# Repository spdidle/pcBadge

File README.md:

# Fallout PCB Badge!
haii this pcb badge is a stupidly simple camera so you can clip your friends and keep the memory forever :p

# Schematic

# PCB 1

# PCB 2

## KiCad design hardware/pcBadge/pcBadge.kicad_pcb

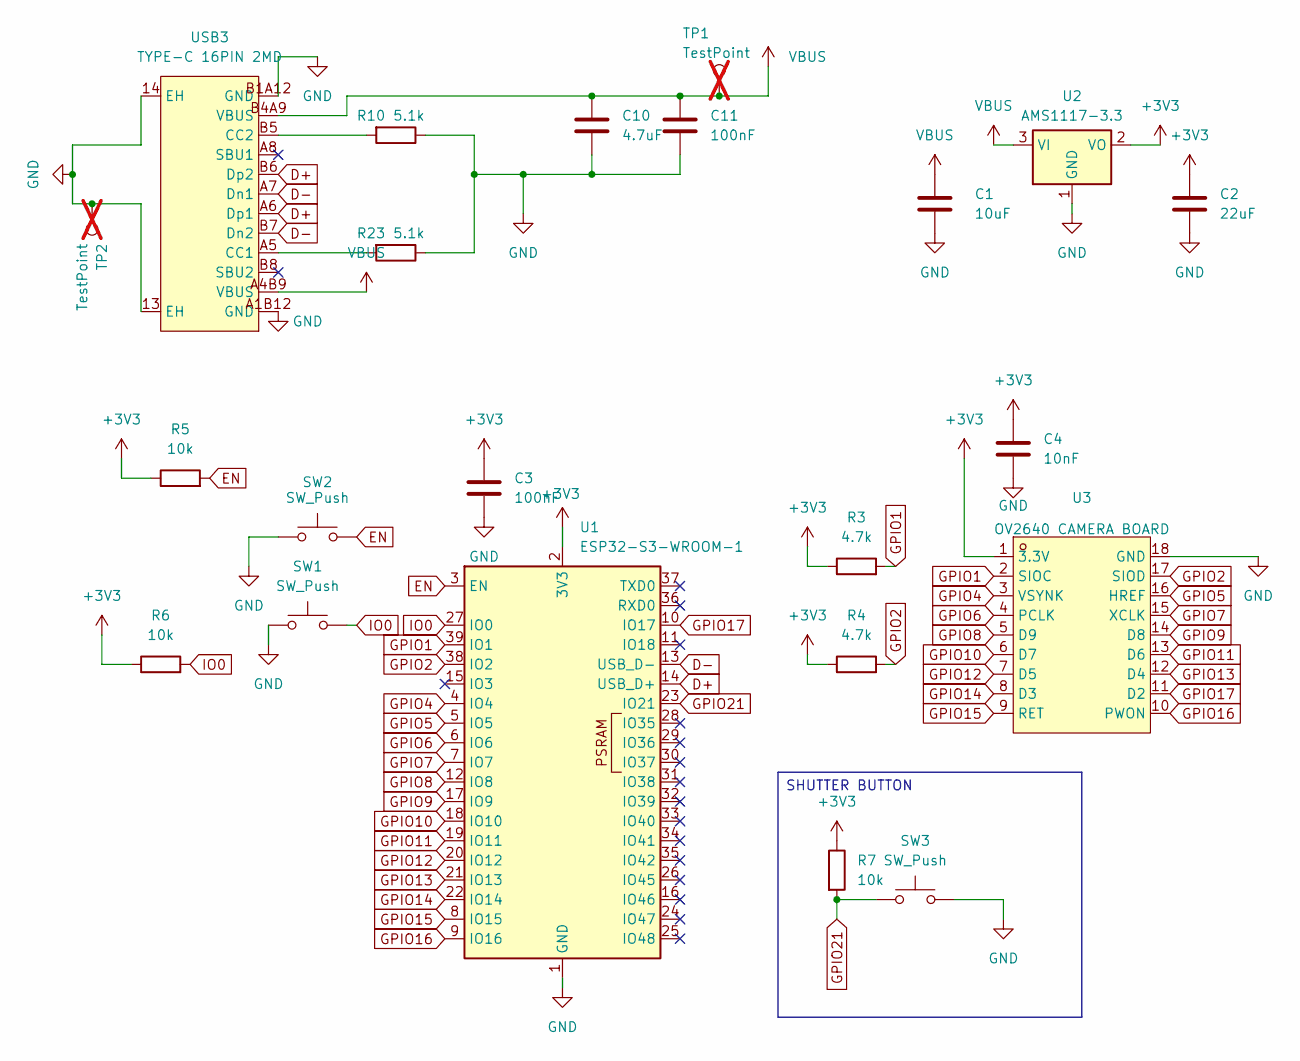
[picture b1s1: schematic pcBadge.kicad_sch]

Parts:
C1: 10uF; C_0805_2012Metric_Pad1.18x1.45mm_HandSolder
C2: 22uF; C_0805_2012Metric_Pad1.18x1.45mm_HandSolder
C3: 100nF; C_0805_2012Metric_Pad1.18x1.45mm_HandSolder
C4: 10nF; C_0805_2012Metric_Pad1.18x1.45mm_HandSolder
C10: 4.7uF; C_0805_2012Metric
C11: 100nF; C_0805_2012Metric
R3, R4: 4.7k; R_0805_2012Metric_Pad1.20x1.40mm_HandSolder
R5, R6, R7: 10k; R_0805_2012Metric_Pad1.20x1.40mm_HandSolder
R10, R23: 5.1k; R_0805_2012Metric
SW1, SW2: SW_Push; SW_Push_SPST_NO_Alps_SKRK
SW3: SW_Push; SW_PUSH-12mm
TP1, TP2: TestPoint; TestPoint_Pad_D1.0mm; not fitted
U1: ESP32-S3-WROOM-1
U2: AMS1117-3.3; SOT-223-3_TabPin2
U3: OV2640 CAMERA BOARD; SENSORM-TH_L35.7-W3.9-OV2640; MPN OV2640 Camera Board; LCSC Part C359962
USB3: TYPE-C 16PIN 2MD; USB-C-SMD_TYPE-C-16PIN-2MD-073; MPN TYPE-C 16PIN 2MD(073); LCSC Part C2765186

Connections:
+3V3: C2.1, C3.1, C4.1, R3.1, R4.1, R5.1, R6.1, R7.1, U1.2 (3V3), U2.2 (VO), U3.1 (3.3V)
D+: U1.14 (USB_D+), USB3.A6 (Dp1), USB3.B6 (Dp2)
D-: U1.13 (USB_D-), USB3.A7 (Dn1), USB3.B7 (Dn2)
EN: R5.2, SW2.2, U1.3 (EN)
GND: C1.2, C2.2, C3.2, C4.2, C10.1, C11.2, R10.1, R23.1, SW1.1, SW2.1, SW3.2, TP2.1 (1_1), U1.1 (GND), U1.40 (GND), U1.41 (GND), U2.1 (GND), U3.18 (GND), USB3.13 (EH), USB3.14 (EH), USB3.A1B12 (GND), USB3.B1A12 (GND)
GPIO1: R3.2, U1.39 (IO1), U3.2 (SIOC)
GPIO2: R4.2, U1.38 (IO2), U3.17 (SIOD)
GPIO4: U1.4 (IO4), U3.3 (VSYNK)
GPIO5: U1.5 (IO5), U3.16 (HREF)
GPIO6: U1.6 (IO6), U3.4 (PCLK)
GPIO7: U1.7 (IO7), U3.15 (XCLK)
GPIO8: U1.12 (IO8), U3.5 (D9)
GPIO9: U1.17 (IO9), U3.14 (D8)
GPIO10: U1.18 (IO10), U3.6 (D7)
GPIO11: U1.19 (IO11), U3.13 (D6)
GPIO12: U1.20 (IO12), U3.7 (D5)
GPIO13: U1.21 (IO13), U3.12 (D4)
GPIO14: U1.22 (IO14), U3.8 (D3)
GPIO15: U1.8 (IO15), U3.9 (RET)
GPIO16: U1.9 (IO16), U3.10 (PWON)
GPIO17: U1.10 (IO17), U3.11 (D2)
GPIO21: R7.2, SW3.1, U1.23 (IO21)
IO0: R6.2, SW1.2, U1.27 (IO0)
unnamed: R23.2, USB3.A5 (CC1)
unnamed: R10.2, USB3.B5 (CC2)
VBUS: C1.1, C10.2, C11.1, TP1.1 (1_1), U2.3 (VI), USB3.A4B9 (VBUS), USB3.B4A9 (VBUS)

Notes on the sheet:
SHUTTER BUTTON

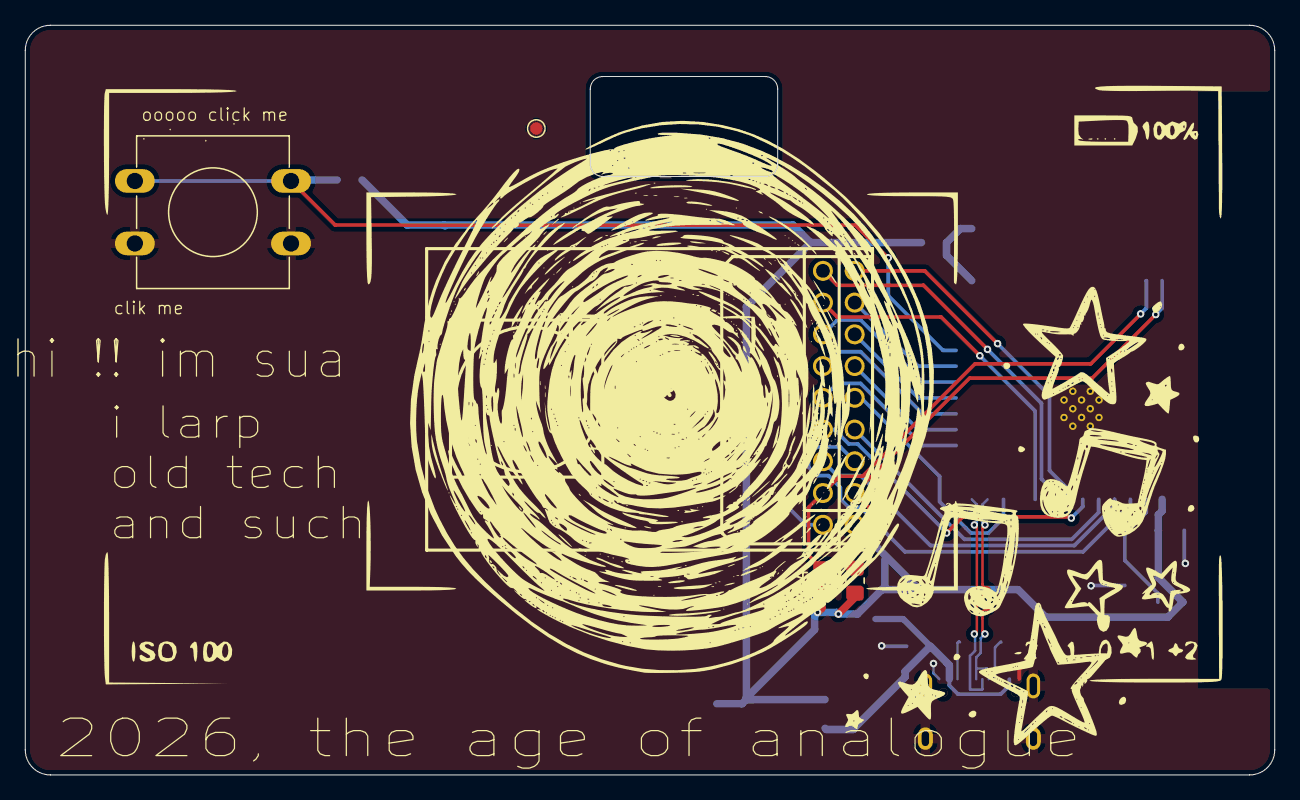
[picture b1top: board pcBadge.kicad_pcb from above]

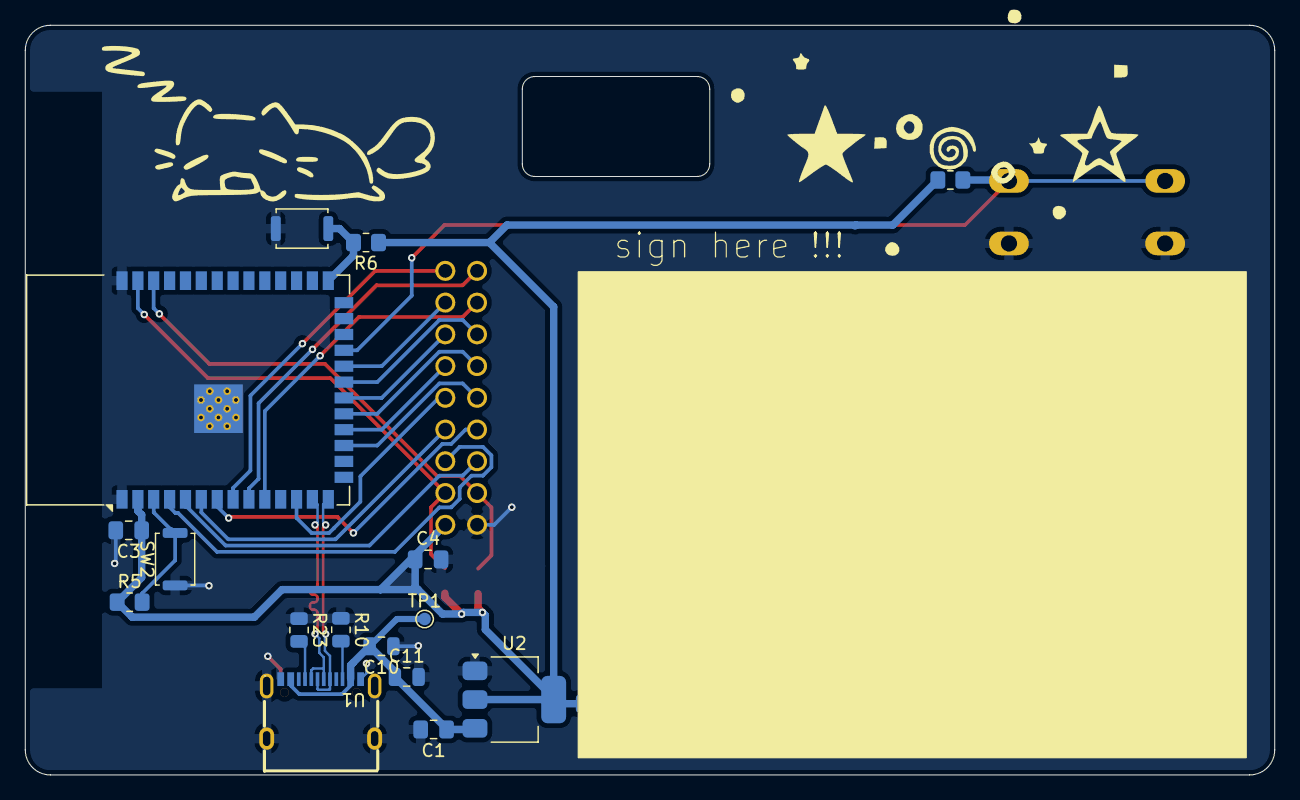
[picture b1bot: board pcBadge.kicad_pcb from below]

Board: 2 copper layers, 100.0 x 60.0 mm, 22 parts (17 on the bottom side), 26 nets.
